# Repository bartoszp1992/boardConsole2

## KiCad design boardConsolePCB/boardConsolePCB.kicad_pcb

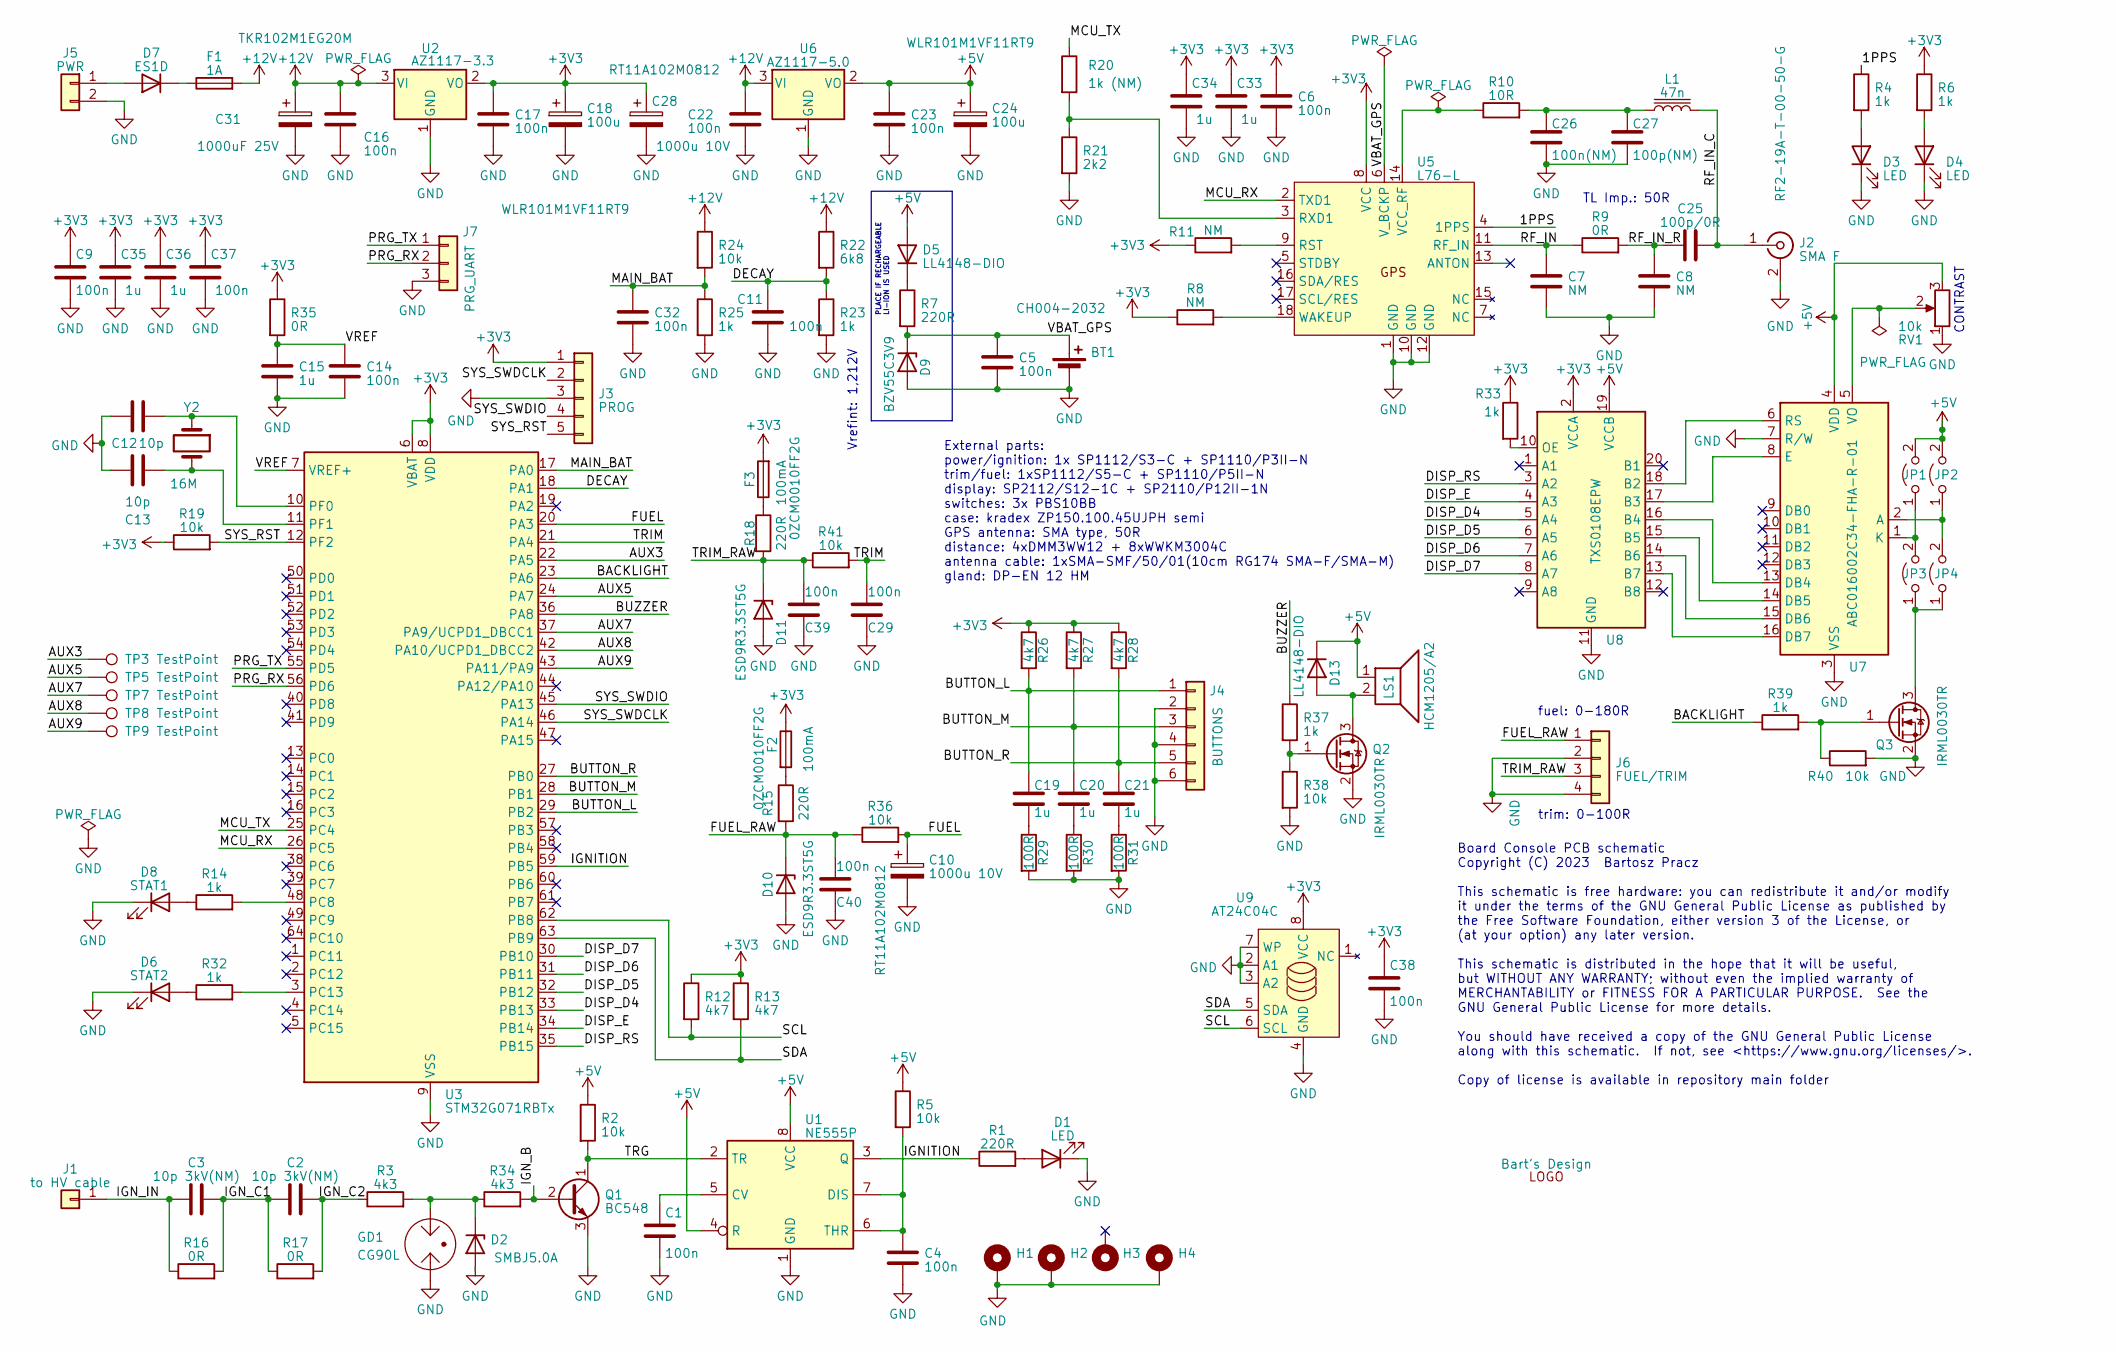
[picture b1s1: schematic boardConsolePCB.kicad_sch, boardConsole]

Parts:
BT1: CH004-2032; BatteryHolder_Keystone_1060_1x2032
C1, C4, C5, C6, C9, C11, C14, C16, C17, C22, C23, C29, C32, C37, C38, C39, C40: 100n; C_0603_1608Metric
C2, C3: 10p 3kV(NM); C_Disc_D8.0mm_W5.0mm_P7.50mm
C7, C8: NM; C_0603_1608Metric
C10, C28: 1000u 10V; CP_D8mm_H13mm_P3.5mm_horizontal
C12, C13: 10p; C_0603_1608Metric
C15, C19, C20, C21, C33, C34, C35, C36: 1u; C_0603_1608Metric
C18, C24: 100u; CP_D8mm_H13mm_P3.5mm_horizontal
C25: 100p/0R; C_0603_1608Metric
C26: 100n(NM); C_0603_1608Metric
C27: 100p(NM); C_0603_1608Metric
C31: 1000uF 25V; CP_D12.5mm_H22mm_P5.0mm_horizontal
D1, D3, D4: LED; LED_0603_1608Metric
D2: SMBJ5.0A; D_SMB
D5, D13: LL4148-DIO; D_MiniMELF
D6: STAT2; LED_0603_1608Metric
D7: ES1D; D_SMA
D8: STAT1; LED_0603_1608Metric
D9: BZV55C3V9; D_MiniMELF
D10, D11: ESD9R3.3ST5G; D_SOD-923
F1: 1A; Fuse_1206_3216Metric
F2, F3: 100mA; Fuse_0603_1608Metric
GD1: CG90L
H1, H2, H3, H4: MountingHole_Pad; MountingHole_3.2mm_M3_Pad
J1: to HV cable; PinHeader_1x01_P2.54mm_Vertical
J2: SMA F; SMA-F
J3: PROG; PinHeader_1x05_P2.54mm_Vertical
J4: BUTTONS; PinHeader_1x06_P2.54mm_Vertical
J5: PWR; PinHeader_1x02_P2.54mm_Vertical
J6: FUEL/TRIM; PinHeader_1x04_P2.54mm_Vertical
J7: PRG_UART; PinHeader_1x03_P2.54mm_Vertical
JP1, JP2, JP3, JP4: Jumper_2_Open; SolderJumper-2_P1.3mm_Open_TrianglePad1.0x1.5mm
L1: 47n; C_0603_1608Metric
LS1: HCM1205/A2; Buzzer_12x9.5RM7.6
Q1: BC548; TO-92_Inline
Q2, Q3: IRML0030TR; SOT-23
R1: 220R; R_0805_2012Metric
R2, R5, R19, R24, R36, R38, R40, R41: 10k; R_0603_1608Metric
R3, R34: 4k3; R_2512_6332Metric
R4, R6, R14, R23, R25, R32, R33, R37, R39: 1k; R_0603_1608Metric
R7, R15, R18: 220R; R_1206_3216Metric
R8, R11: NM; R_0603_1608Metric
R9, R35: 0R; R_0603_1608Metric
R10: 10R; R_0603_1608Metric
R12, R13, R26, R27, R28: 4k7; R_0603_1608Metric
R16, R17: 0R; R_2512_6332Metric
R20: 1k (NM); R_0603_1608Metric
R21: 2k2; R_0603_1608Metric
R22: 6k8; R_0603_1608Metric
R29, R30, R31: 100R; R_0805_2012Metric
RV1: 10k; Potentiometer_ACP_CA9-H5_Horizontal
TP3, TP5, TP7, TP8, TP9: TestPoint; TestPoint_Pad_2.0x2.0mm
U1: NE555P; DIP-8_W7.62mm
U2: AZ1117-3.3; TO-252-2
U3: STM32G071RBTx; LQFP-64_10x10mm_P0.5mm
U5: L76-L
U6: AZ1117-5.0; TO-252-2
U7: ABC016002C34-FHA-R-01; WH1602L1-YYH-CT010
U8: TXS0108EPW; TSSOP-20_4.4x6.5mm_P0.65mm
U9: AT24C04C; DIP-8_W7.62mm
X1: Bart's Design; BD_full 20x5.2
Y2: 16M; Crystal_SMD_HC49-SD

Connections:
+3V3: C6.1, C9.1, C17.1, C18.1, C28.1, C33.1, C34.1, C35.1, C36.1, C37.1, C38.1, F2.1, F3.2, J3.1, R6.1, R8.1, R11.1, R12.1, R13.1, R19.1, R26.1, R27.1, R28.1, R33.1, R35.1, U2.2 (VO), U3.6 (VBAT), U3.8 (VDD), U5.8 (VCC), U8.2 (VCCA), U9.8 (VCC)
+5V: C23.1, C24.1, D5.2 (A), D13.1 (K), JP1.2 (B), JP2.2 (B), LS1.1, R2.1, R5.1, RV1.3, U1.4 (R), U1.8 (VCC), U6.2 (VO), U7.4 (VDD), U8.19 (VCCB)
+12V: C16.1, C22.1, C31.1, F1.2, R22.1, R24.1, U2.3 (VI), U6.3 (VI)
/1PPS: R4.1, U5.4 (1PPS)
/AUX3: TP3.1, U3.22 (PA5)
/AUX5: TP5.1, U3.24 (PA7)
/AUX7: TP7.1, U3.37 (PA9/UCPD1_DBCC1)
/AUX8: TP8.1, U3.42 (PA10/UCPD1_DBCC2)
/AUX9: TP9.1, U3.43 (PA11/PA9)
/BACKLIGHT: R39.1, U3.23 (PA6)
/BUTTON_L: C19.1, J4.1, R26.2, U3.29 (PB2)
/BUTTON_M: C20.1, J4.3, R27.2, U3.28 (PB1)
/BUTTON_R: C21.1, J4.5, R28.2, U3.27 (PB0)
/BUZZER: R37.1, U3.36 (PA8)
/DECAY: C11.1, R22.2, R23.1, U3.18 (PA1)
/DISP_D4: U3.33 (PB13), U8.5 (A4)
/DISP_D5: U3.32 (PB12), U8.6 (A5)
/DISP_D6: U3.31 (PB11), U8.7 (A6)
/DISP_D7: U3.30 (PB10), U8.8 (A7)
/DISP_E: U3.34 (PB14), U8.4 (A3)
/DISP_RS: U3.35 (PB15), U8.3 (A2)
/FUEL: C10.1, R36.2, U3.20 (PA3)
/FUEL_RAW: C40.1, D10.1 (K), J6.1, R15.2, R36.1
/IGNITION: R1.1, U1.3 (Q), U3.59 (PB5)
/IGN_B: Q1.2 (B), R34.2
/IGN_C1: C2.1, C3.2, R16.2, R17.1
/IGN_C2: C2.2, R3.1, R17.2
/IGN_IN: C3.1, J1.1, R16.1
/MAIN_BAT: C32.1, R24.2, R25.1, U3.17 (PA0)
/MCU_RX: U3.26 (PC5), U5.2 (TXD1)
/MCU_TX: R20.1, U3.25 (PC4)
/PRG_RX: J7.2, U3.56 (PD6)
/PRG_TX: J7.1, U3.55 (PD5)
/RF_IN: C7.1, R9.1, U5.11 (RF_IN)
/RF_IN_C: C25.2, J2.1 (In), L1.2
/RF_IN_R: C8.1, C25.1, R9.2
/SCL: R12.2, U3.62 (PB8), U9.6 (SCL)
/SDA: R13.2, U3.63 (PB9), U9.5 (SDA)
/SYS_RST: J3.5, R19.2, U3.12 (PF2)
/SYS_SWDCLK: J3.2, U3.46 (PA14)
/SYS_SWDIO: J3.4, U3.45 (PA13)
/TRG: Q1.1 (C), R2.2, U1.2 (TR)
/TRIM: C29.1, R41.2, U3.21 (PA4)
/TRIM_RAW: C39.1, D11.1 (K), J6.3, R18.2, R41.1
/VBAT_GPS: BT1.1 (+), C5.1, D9.1 (K), R7.2, U5.6 (V_BCKP)
/VREF: C14.1, C15.1, R35.2, U3.7 (VREF+)
GND: BT1.2 (-), C1.2, C4.2, C5.2, C6.2, C7.2, C8.2, C9.2, C10.2, C11.2, C12.1, C13.1, C14.2, C15.2, C16.2, C17.2, C18.2, C22.2, C23.2, C24.2, C26.2, C27.2, C28.2, C29.2, C31.2, C32.2, C33.2, C34.2, C35.2, C36.2, C37.2, C38.2, C39.2, C40.2, D1.1 (K), D2.2 (A), D3.1 (K), D4.1 (K), D6.1 (K), D8.1 (K), D9.2 (A), D10.2 (A), D11.2 (A), GD1.1, H1.1, H2.1, H4.1, J2.2 (Ext), J3.3, J4.2, J4.4, J4.6, J5.2, J6.2, J6.4, J7.3, Q1.3 (E), Q2.2 (S), Q3.2 (S), R21.2, R23.2, R25.2, R29.2, R30.2, R31.2, R38.2, R40.2, RV1.1, U1.1 (GND), U2.1 (GND), U3.9 (VSS), U5.1 (GND), U5.10 (GND), U5.12 (GND), U6.1 (GND), U7.3 (VSS), U7.7 (R/W), U8.11 (GND), U9.2 (A1), U9.3 (A2), U9.4 (GND), U9.7 (WP)
unnamed: C19.2, R29.1
unnamed: C20.2, R30.1
unnamed: C21.2, R31.1
unnamed: C26.1, C27.1, L1.1, R10.2
unnamed: D1.2 (A), R1.2
unnamed: D2.1 (K), GD1.3, R3.2, R34.1
unnamed: D3.2 (A), R4.2
unnamed: D4.2 (A), R6.2
unnamed: D5.1 (K), R7.1
unnamed: D6.2 (A), R32.1
unnamed: D7.2 (A), J5.1
unnamed: D7.1 (K), F1.1
unnamed: D8.2 (A), R14.1
unnamed: D13.2 (A), LS1.2, Q2.3 (D)
unnamed: F2.2, R15.1
unnamed: F3.1, R18.1
unnamed: JP1.1 (A), JP3.2 (B), U7.1 (K)
unnamed: JP2.1 (A), JP4.2 (B), U7.2 (A)
unnamed: JP3.1 (A), JP4.1 (A), Q3.3 (D)
unnamed: Q2.1 (G), R37.2, R38.1
unnamed: Q3.1 (G), R39.2, R40.1
unnamed: C1.1, U1.5 (CV)
unnamed: C4.1, R5.2, U1.6 (THR), U1.7 (DIS)
unnamed: R14.2, U3.48 (PC8)
unnamed: R32.2, U3.3 (PC13)
unnamed: C12.2, U3.10 (PF0), Y2.1
unnamed: C13.2, U3.11 (PF1), Y2.2
unnamed: R11.2, U5.9 (RST)
unnamed: R20.2, R21.1, U5.3 (RXD1)
unnamed: R10.1, U5.14 (VCC_RF)
unnamed: R8.2, U5.18 (WAKEUP)
unnamed: U7.13 (DB4), U8.16 (B4)
unnamed: U7.14 (DB5), U8.15 (B5)
unnamed: U7.15 (DB6), U8.14 (B6)
unnamed: U7.16 (DB7), U8.13 (B7)
unnamed: U7.8 (E), U8.17 (B3)
unnamed: U7.6 (RS), U8.18 (B2)
unnamed: RV1.2, U7.5 (VO)
unnamed: R33.2, U8.10 (OE)

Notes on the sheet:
External parts: power/ignition: 1x SP1112/S3-C + SP1110/P3II-N trim/fuel: 1xSP1112/S5-C + SP1110/P5II-N display: SP2112/S12-1C + SP2110/P12II-1N switches: 3x PBS10BB case: kradex ZP150.100.45UJPH semi GPS antenna: SMA type, 50R distance: 4xDMM3WW12 + 8xWWKM3004C antenna cable: 1xSMA-SMF/50/01(10cm 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
Board Console PCB schematic Copyright (C) 2023 Bartosz Pracz This schematic is free hardware: you can redistribute it and/or modify it under the terms of the GNU General Public License as published by the Free Software Foundation, either version 3 of the License, or (at your option) any later versi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
trim: 0-100R
PLACE IF RECHARGEABLE LI-ION IS USED
CONTRAST
Vrefint: 1,212V
fuel: 0-180R
TL Imp.: 50R

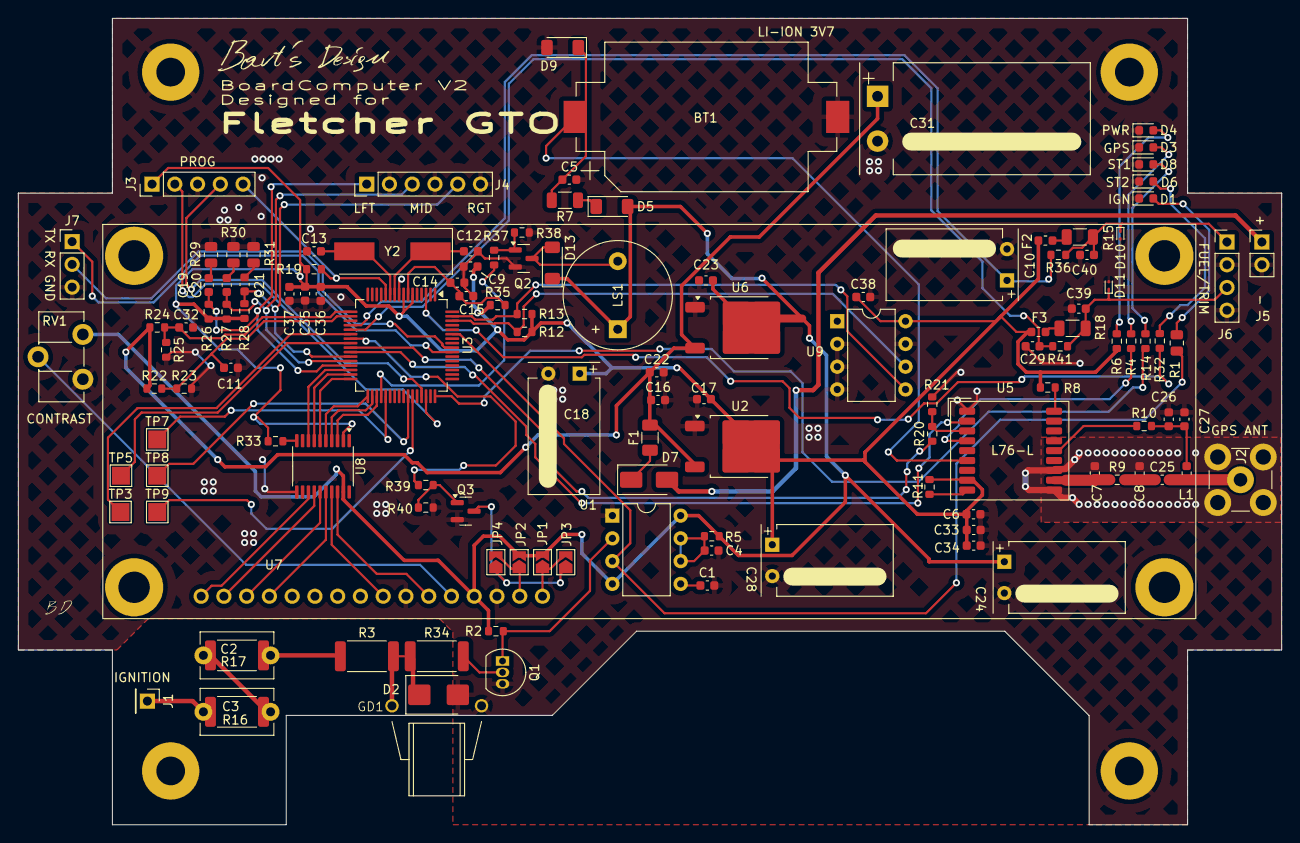
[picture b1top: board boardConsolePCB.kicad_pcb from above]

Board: 2 copper layers, 141.0 x 90.0 mm, 133 parts (0 on the bottom side), 86 nets.

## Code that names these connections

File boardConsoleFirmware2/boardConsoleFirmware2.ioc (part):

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Mcu.Name=STM32G071R(6-8-B)Tx
Mcu.Package=LQFP64
Mcu.UserName=STM32G071RBTx
PA0.GPIOParameters=GPIO_Label
PA0.GPIO_Label=ADC_BAT
PA0.Mode=IN0
PA0.Signal=ADC1_IN0
PA1.GPIOParameters=GPIO_Label
PA1.GPIO_Label=DECAY
PA1.Mode=INP
PA1.Signal=COMP1_INP
PA13.Mode=Serial_Wire
PA13.Signal=SYS_SWDIO
PA14-BOOT0.Mode=Serial_Wire
PA14-BOOT0.Signal=SYS_SWCLK
PA3.GPIOParameters=GPIO_Label
PA3.GPIO_Label=ADC_FUEL
PA3.Mode=IN3
PA3.Signal=ADC1_IN3
PA4.GPIOParameters=GPIO_Label
PA4.GPIO_Label=ADC_TRIM
PA4.Mode=IN4
PA4.Signal=ADC1_IN4
PA5.GPIOParameters=GPIO_Label
PA5.GPIO_Label=TEST
PA5.Signal=GPIO_Output
PA6.GPIOParameters=GPIO_Label
PA6.GPIO_Label=BACKLIGHT
PA6.Signal=S_TIM3_CH1
PA8.GPIOParameters=GPIO_Label
PA8.GPIO_Label=BUZZER
PA8.Signal=GPIO_Output
PB0.GPIOParameters=GPIO_Label
PB0.GPIO_Label=BUTTON_R
PB0.Signal=GPIO_Input
PB1.GPIOParameters=GPIO_Label
PB1.GPIO_Label=BUTTON_M
PB1.Signal=GPIO_Input
PB10.GPIOParameters=GPIO_Label
PB10.GPIO_Label=LCD_DB7
PB10.Signal=GPIO_Output
PB11.GPIOParameters=GPIO_Label
PB11.GPIO_Label=LCD_DB6
PB11.Signal=GPIO_Output
PB12.GPIOParameters=GPIO_Label
PB12.GPIO_Label=LCD_DB5
PB12.Signal=GPIO_Output
PB13.GPIOParameters=GPIO_Label
PB13.GPIO_Label=LCD_DB4
PB13.Signal=GPIO_Output
PB14.GPIOParameters=GPIO_Label
PB14.GPIO_Label=LCD_E
PB14.Signal=GPIO_Output
PB15.GPIOParameters=GPIO_Label
PB15.GPIO_Label=LCD_RS
PB15.Signal=GPIO_Output
PB2.GPIOParameters=GPIO_Label
PB2.GPIO_Label=BUTTON_L
PB2.Signal=GPIO_Input
PB5.GPIOParameters=GPIO_Label,GPIO_ModeDefaultEXTI
PB5.GPIO_Label=IGNITION
PB5.GPIO_ModeDefaultEXTI=GPIO_MODE_IT_RISING_FALLING
PB5.Signal=GPXTI5
PB8.Mode=I2C
PB8.Signal=I2C1_SCL
PB9.Mode=I2C
PB9.Signal=I2C1_SDA
PC13.GPIOParameters=GPIO_Label
PC13.GPIO_Label=LED_STAT2
PC13.Signal=GPIO_Output
PC14-OSC32_IN\ (PC14).Mode=LSE-External-Oscillator
PC14-OSC32_IN\ (PC14).Signal=RCC_OSC32_IN
PC15-OSC32_OUT\ (PC15).Mode=LSE-External-Oscillator
PC15-OSC32_OUT\ (PC15).Signal=RCC_OSC32_OUT
PC4.Mode=Asynchronous
PC4.Signal=USART1_TX
PC5.Mode=Asynchronous
PC5.Signal=USART1_RX
PC8.GPIOParameters=GPIO_Label
PC8.GPIO_Label=LED_STAT1
PC8.Signal=GPIO_Output
PD5.Mode=Asynchronous
PD5.Signal=USART2_TX
PD6.Mode=Asynchronous
PD6.Signal=USART2_RX
PF0-OSC_IN\ (PF0).Mode=HSE-External-Oscillator
PF0-OSC_IN\ (PF0).Signal=RCC_OSC_IN
PF1-OSC_OUT\ (PF1).Mode=HSE-External-Oscillator
PF1-OSC_OUT\ (PF1).Signal=RCC_OSC_OUT
RCC.HSE_VALUE=16000000
RCC.SYSCLKFreq_VALUE=64000000
RCC.SYSCLKSource=RCC_SYSCLKSOURCE_PLLCLK
board=custom

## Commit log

2023-12-22 initial
2024-01-24 added manu map
2024-02-02 add speedo unit setting
2024-02-03 speedo kmh fix
2024-02-26 correct values for polarized caps
2024-02-26 correct description for antenna TL
2024-02-27 update pdf schematic
2024-04-27 add working low fuel alert, add display re-init
2024-04-27 low fuel alert fix
2024-06-08 add GDT
2024-12-17 dont know
2024-12-17 add shade
2024-12-17 smaller shade
